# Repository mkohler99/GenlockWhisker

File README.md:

# Genlock Whisker

# Exciting Updates!
Now with a web serial UI. Simply host the contents of the 'web' folder somewhere and open the page with Chrome (or maybe Edge? Safari does not allow web serial which makes me sad because web serial is pretty awesome) . UPDATE: Hosted here for now https://genlockwhisker.pages.dev again, this has only been tested in chrome.  TBD I *think* this requires HTTPS and you cant just open the HTML on your local machine but id love to be wrong. Anyway, the Web UI adds easier to read monitoring as well as an attempt at monitoring the statistics over time. Im trying to verify how useful ANY of these jitter measurments are and would love if anyone has......a bad genlock source that has lots of jitter to test with?

# About
The genlock whisker is an expansion module for the FUSE CATS Frame:Work 2025 NYC Pixel Kitty conference badge that allows you to turn your badge into a genlock tester. 
The device reads most types of genlock signals on an HDBNC connector and displays information about them on the badge's RGB Pixel Matrix Display.

# Current features:
- Detects Bi-Level or Tri-Level sync by displaying green for Bi-Level and blue for Tri-Level. Detects no sync or unstable sync by displaying "NO LOCK" in red
- Displays Frame rate of sync up to 3 decimal places
- Outputs sync drift statistics over USB type C serial connection

- Hardware fix for This latest code release.

Cut the indicated Pin in order to un-short the HSYNC IO Pin. Since this is actually a bug in the base Pixel Kitty Badge Board, its hard to fix perfectly since the problem can be in either place. for now, the easiest fix is to remove one header pin from the expansion module which prevents the HSYNC pin on the LMH1980 from grounding out and not being able to read. because this new version improves data gathering by detecting HSYNC lines and counting them in order to determine the signal format, this version of software will not work without the hardware mod. 

Because Safety is our number 1 priority, please wear safety goggles when cutting the pin as it can fly anywhere.

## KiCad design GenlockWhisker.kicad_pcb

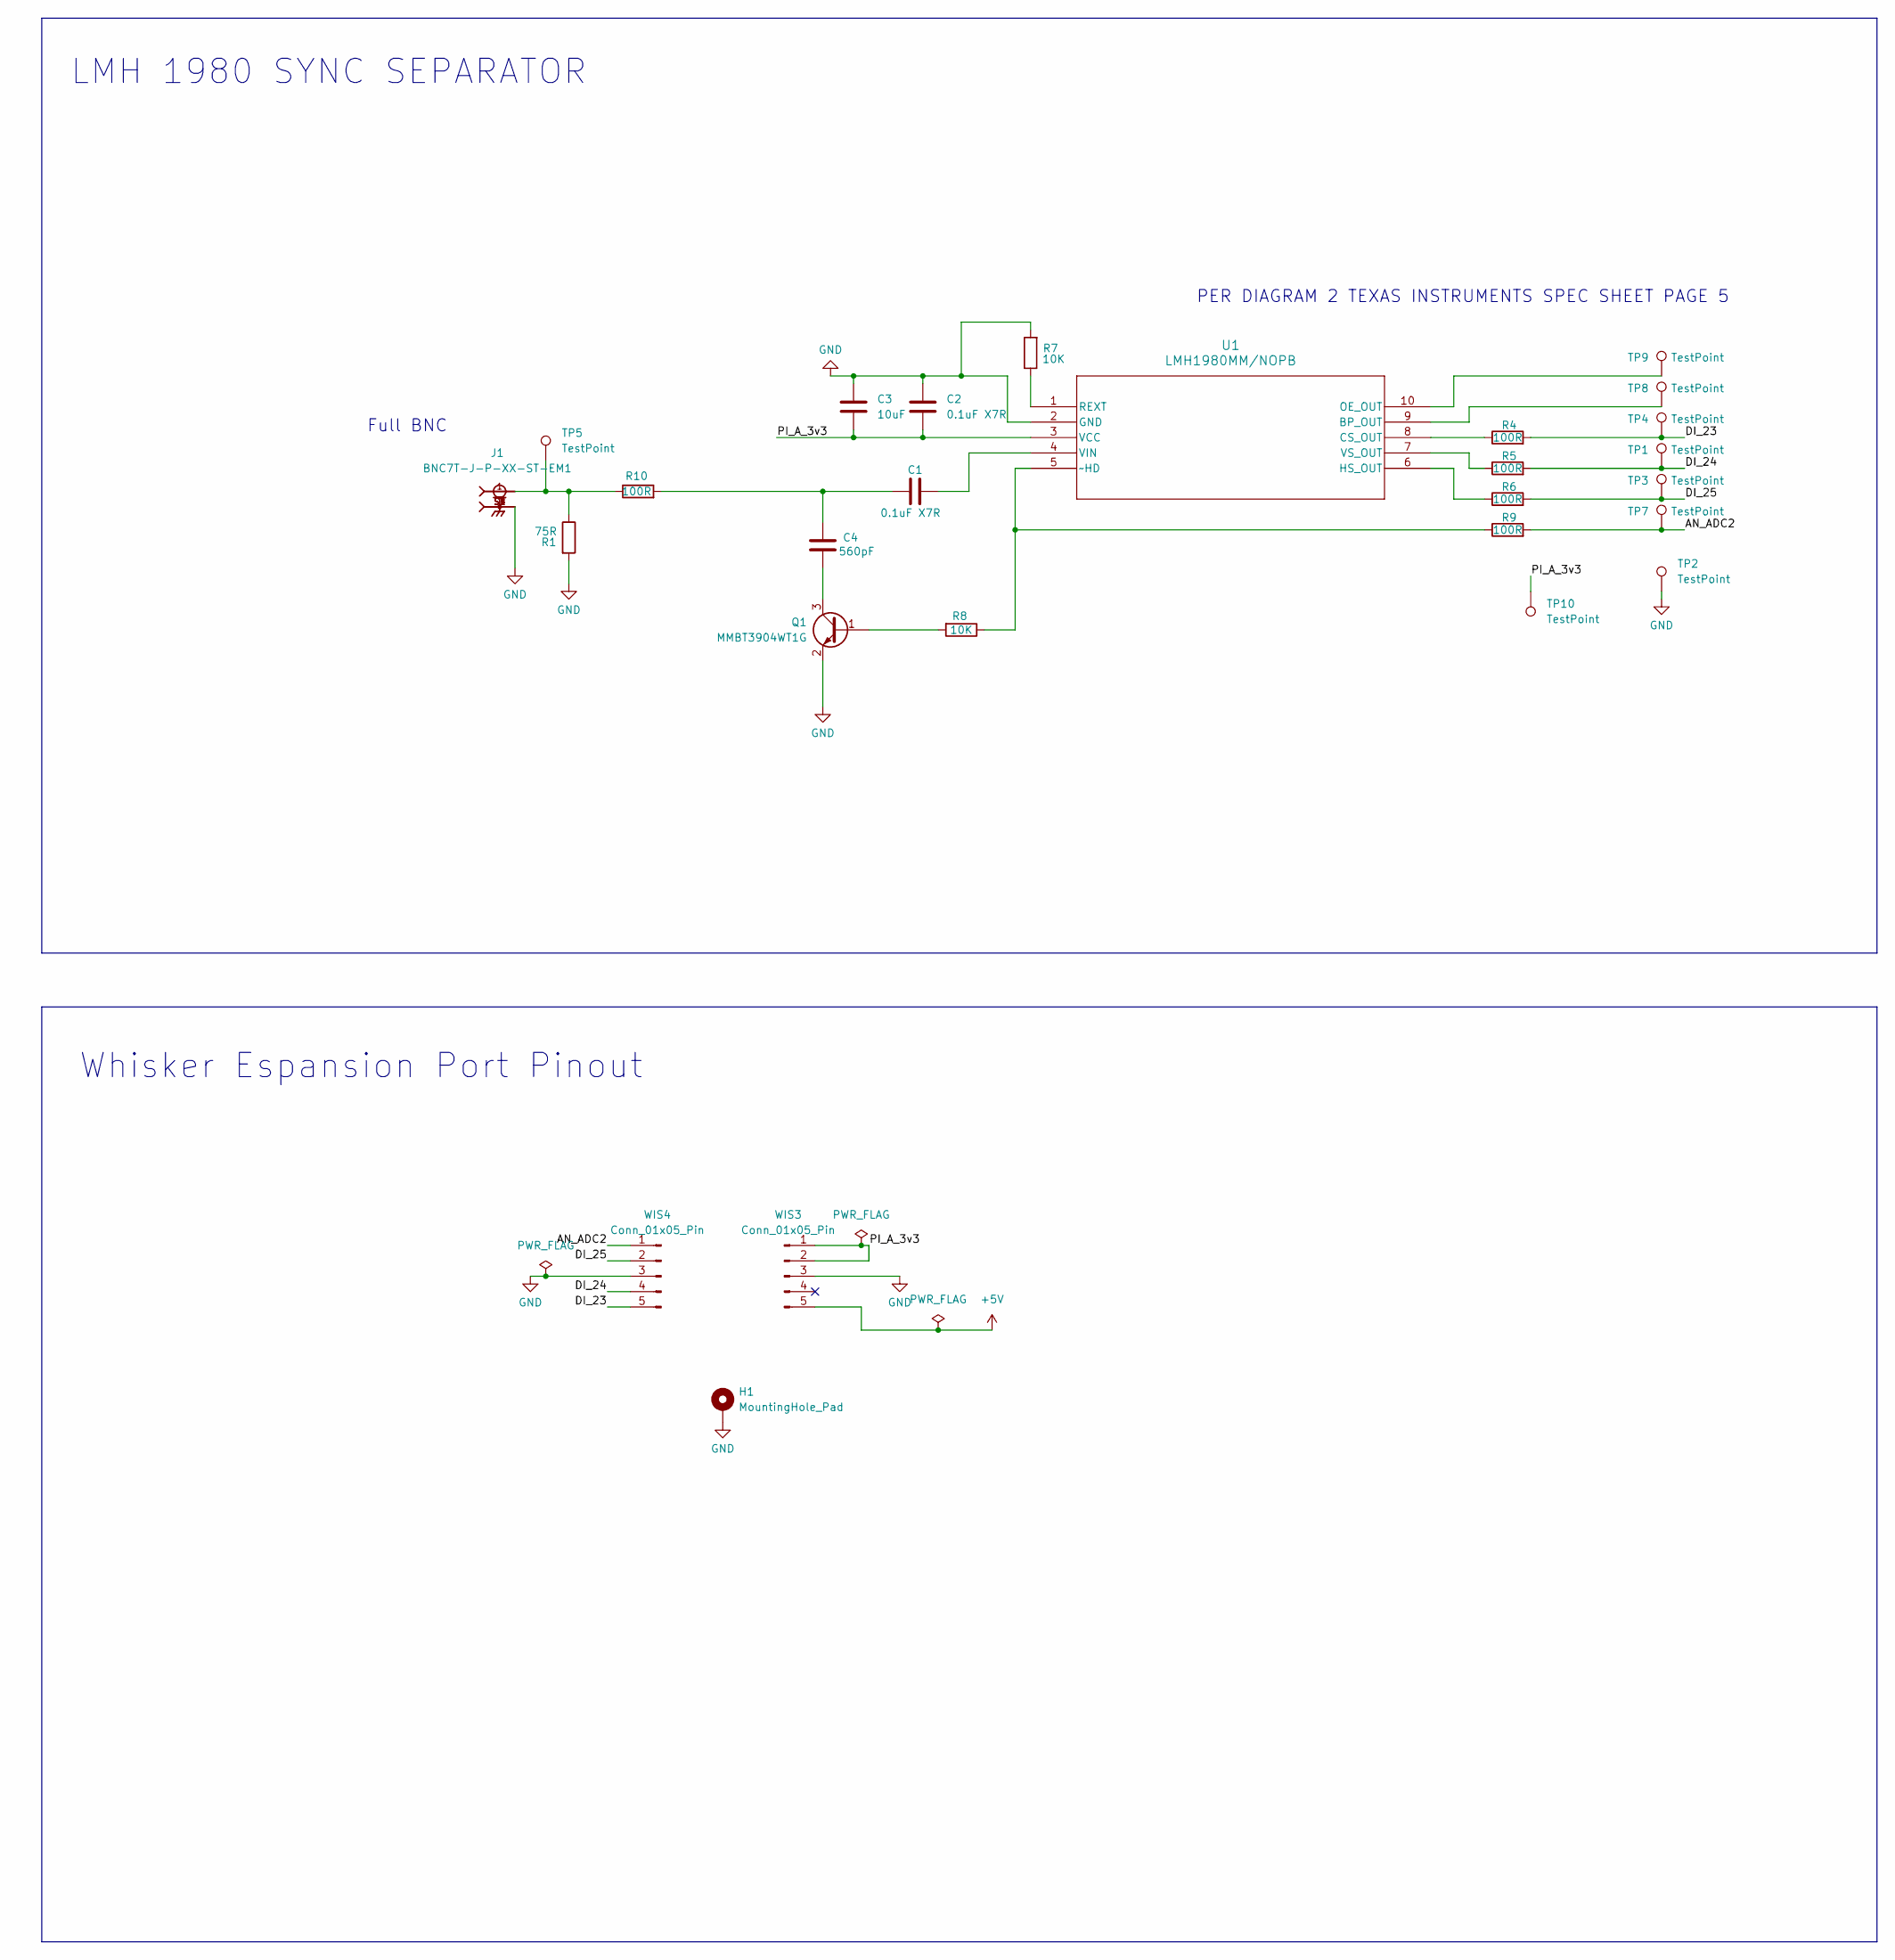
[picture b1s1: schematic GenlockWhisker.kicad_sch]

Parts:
C1, C2: 0.1uF X7R; C_0603_1608Metric; LCSC C14663
C3: 10uF; C_0603_1608Metric; LCSC C19702
C4: 560pF; C_0603_1608Metric; LCSC C1627
H1: MountingHole_Pad; MountingHole_2.7mm_M2.5_DIN965_Pad; LCSC DNP
J1: BNC7T-J-P-XX-ST-EM1; SAMTEC_BNC7T-J-P-XX-ST-EM1D; PARTREV E; LCSC C3173636
Q1: MMBT3904WT1G; SOT-23; LCSC C58011
R1: 75R; R_0603_1608Metric; LCSC C4275
R4, R5, R6, R9, R10: 100R; R_0603_1608Metric; LCSC C22775
R7, R8: 10K; R_0603_1608Metric; LCSC C21190
TP1, TP2, TP3, TP4, TP5, TP7, TP8, TP9, TP10: TestPoint; TestPoint_Pad_1.5x1.5mm; LCSC DNP
U1: LMH1980MM/NOPB; MUB10A; LCSC C189203
WIS3, WIS4: Conn_01x05_Pin; PinHeader_1x05_P2.54mm_Vertical; LCSC DNP

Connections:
+5V: WIS3.5
/AN_ADC2: R9.2, TP7.1, WIS4.1
/DI_23: R4.2, TP4.1, WIS4.5
/DI_24: R5.2, TP1.1, WIS4.4
/DI_25: R6.2, TP3.1, WIS4.2
/PI_A_3v3: C2.1, C3.1, TP10.1, U1.3 (VCC), WIS3.1, WIS3.2
GND: C2.2, C3.2, H1.1, J1.S1, J1.S2, J1.S3, J1.S4, Q1.2 (E), R1.2, R7.2, TP2.1, U1.2 (GND), WIS3.3, WIS4.3
unnamed: C1.1, C4.2, R10.2
unnamed: J1.1, R1.1, R10.1, TP5.1
unnamed: Q1.1 (B), R8.2
unnamed: C4.1, Q1.3 (C)
unnamed: TP8.1, U1.9 (BP_OUT)
unnamed: R4.1, U1.8 (CS_OUT)
unnamed: R6.1, U1.6 (HS_OUT)
unnamed: TP9.1, U1.10 (OE_OUT)
unnamed: R7.1, U1.1 (REXT)
unnamed: C1.2, U1.4 (VIN)
unnamed: R5.1, U1.7 (VS_OUT)
unnamed: R8.1, R9.1, U1.5 (~HD)

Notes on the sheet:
Full BNC
PER DIAGRAM 2 TEXAS INSTRUMENTS SPEC SHEET PAGE 5
LMH 1980 SYNC SEPARATOR
Whisker Espansion Port Pinout

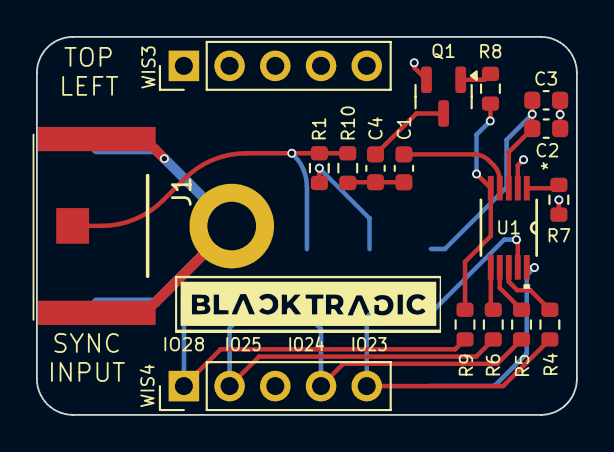
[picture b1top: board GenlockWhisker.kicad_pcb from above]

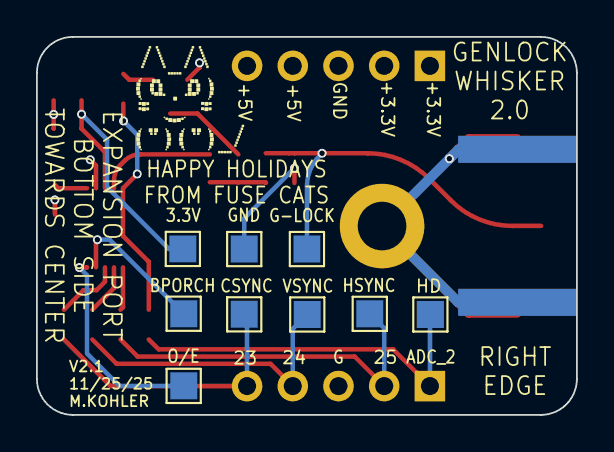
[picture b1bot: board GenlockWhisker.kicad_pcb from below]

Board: 4 copper layers, 30.0 x 21.0 mm, 27 parts (9 on the bottom side), 18 nets.

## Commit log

2025-11-01 Added Software Folder
2025-12-03 New version with full size connector. major software improvements including high frequency logging and webserial UI
2025-12-03 Detail HW Fix to accompany previous Committ
2025-12-03 I dont really know how to write markdown
